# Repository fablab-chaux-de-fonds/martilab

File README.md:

Martilab, fruit d'une collaboration entre le [FabLab Chaux-de-Fonds](fablab-chaux-de-fonds.ch) et le [Muzoo](https://muzoo.ch/) , propose une approche pratique pour encourager la nidification des martinets. En plaçant des haut-parleurs discrets diffusant des signaux sonores adaptés près des nichoirs, nous offrons aux martinets un environnement accueillant et stimulant. Une initiative simple et efficace pour favoriser la préservation de ces oiseaux migrateurs essentiels à notre écosystème. 

<div align="center">

</div>

# Liste des pièces

| | |
| ----------- | ----------- |
|| [Microcontrôleur - Raspberry Pi Pico H](https://www.mouser.ch/ProductDetail/Raspberry-Pi/SC0917?qs=T%252BzbugeAwjjvYEYcRJk%252Bxw%3D%3D): Un microcontrôleur est un dispositif électronique intégré sur une puce (puce microélectronique) qui combine plusieurs composants essentiels pour le traitement de l'information. Il est conçu pour exécuter des tâches spécifiques dans des systèmes électroniques. <br><br>  Le microcontrôleur est le cerveau du martilab. |
||[Horloge temps réel - D1Z RTC - DS1307](https://www.reichelt.com/ch/fr/shield-d1-horloge-temps-r-el-ds1307-d1z-rtc-p266069.html?&trstct=pos_0&nbc=1): Cette horloge temps réel utilise le circuit intégré DS1307 pour fournir une référence temporelle précise à un microcontrôleur. <br><br>  L'horloge permet de connaître le temps absolu et d'activer la l'haut parleur à un moment de la journée.|
||[Piles boutons - CR1220](https://www.reichelt.com/ch/fr/pile-bouton-lithium-c1220-blister-de-5-xcell-cr1220-5x-p365560.html?&trstct=pos_0&nbc=1):  Les piles boutons CR1220 sont des petites piles rondes au lithium. Elles sont souvent utilisées comme source d'alimentation pour des dispositifs électroniques compacts tels que des horloges, des capteurs et d'autres équipements électroniques.  <br><br>  La pile permet à l'horloge de fonctionner même si le contrôleur est en veille. Ainsi, on connait toujours le temps absolu.
||[Lecteur mp3 - DFPlayer Mini](https://www.reichelt.com/ch/fr/arduino-dfplayer-mini-mp3-wav-microsd-karte-ard-dfpayer-mini-p289897.html?&trstct=pos_0&nbc=1): Un lecteur MP3 compact conçu pour être intégré dans des projets électroniques. Il prend en charge la lecture de fichiers audio stockés sur une carte micro SD, offrant une solution simple pour la lecture audio.|
||[Micro haut-parleur - LSM-40A/SQ](https://www.reichelt.com/ch/fr/haut-parleur-en-m-tal-raccord-soud--lsm-40a-sq-p145885.html?&trstct=pos_0&nbc=1): Un micro haut-parleur est un petit haut-parleur conçu pour émettre des sons dans des dispositifs compacts tels que des dispositifs portables, des jouets électroniques, ou d'autres projets électroniques nécessitant une sortie audio.|
||[JST PH 2-Pin Cable Male Header 200mm](https://www.mouser.ch/ProductDetail/Adafruit/3814?qs=%252BEew9%252B0nqrBFmoDCETN4BA%3D%3D): Un câble avec un connecteur mâle JST PH à deux broches de 200 mm de long. Les connecteurs JST PH sont couramment utilisés pour les connexions de puissance ou de données dans les projets électroniques.<br><br> Ce cable permet de relier le lecteur MP3 et le haut-parleur.|
||[Barrette droite à une rangée de broches 2 pôles - JST PH ](https://www.reichelt.com/ch/fr/barrette-droite-une-rang-e-de-broches-2-p-les-grille2-mm-p-les-jst-ph2p-st-p185049.html?&trstct=pos_0&nbc=1): Une barrette de connecteurs droits à une rangée de deux broches, utilisée pour des connexions simples et compactes dans des projets électroniques. Les connecteurs JST PH offrent une connexion sécurisée.<br><br> Connecteur pour le câble, afin de pouvoir facilement débrancher le haut-parleur.
||[Carte micro SDHC](https://www.reichelt.com/ch/fr/carte-micro-sdhc-4-go-intenso-intenso-msdhc4g-p83730.html?&trstct=pos_0&nbc=1): Une carte mémoire au format micro SDHC, utilisée pour stocker des données telles que des fichiers audio, des images ou des données de configuration pour des dispositifs électroniques.|
||[MOSFET PNP -ZVP2106ASTZ](https://eu.mouser.com/ProductDetail/Diodes-Incorporated/ZVP2106ASTZ?qs=wnTfsH77Xs53LehfD70aKA%3D%3D): Un transistor à effet de champ métal-oxyde-semiconducteur (MOSFET) de type PNP, utilisé pour la commutation de puissance dans des circuits électroniques.<br><br>Ce composent permet d'éteindre ([Commutateur à transistor côté haut](https://www.baldengineer.com/low-side-vs-high-side-transistor-switch.html)) le lecteur MP3 lorsque le martilab ne doit pas émettre de son. Ceci permet d'économiser de la batterie.|
||[Boîtier électronique - CB EAC-02-GY](https://www.reichelt.com/ch/fr/bo-tier-lectronique-110-x-70-x-45-mm-gris-cb-eac-02-gy-p317682.html?&trstct=pos_0&nbc=1): Un boîtier électronique conçu pour loger et protéger les composants électroniques d'un projet. Il offre une structure robuste et un espace organisé pour faciliter le montage. 
||[36-pin Male Header Breakaway 10 pieces](https://eu.mouser.com/ProductDetail/Adafruit/392?qs=GURawfaeGuBPkJS%252B96amuQ%3D%3D): Une barrette de connecteurs mâles de 36 broches, pouvant être séparée en sections plus petites. Les headers sont souvent utilisés pour faciliter la connexion entre les cartes électroniques.<br><br> Les pins évitent de devoir souder les dispositifs (Pico, RTC, DFPlayer) afin de pouvoir facilement les recycler et les utiliser dans d'autres projets.|
||[2 x 20 pin Female Headers](https://www.mouser.ch/ProductDetail/Adafruit/5583?qs=T%252BzbugeAwjicPo%2FCTvtw2w%3D%3D): Deux barrettes de connecteurs femelles de 20 broches chacune. Elles sont utilisées pour créer des connexions entre des cartes ou des composants électroniques.

## Option
| | |
| ----------- | ----------- |
| |[LiPo SHIM](https://www.pi-shop.ch/lipo-shim-for-pico): Le LiPo SHIM (Switch Input Module) for Pico est un module conçu spécifiquement pour le Raspberry Pi Pico. Il est destiné à fournir une interface de gestion d'alimentation pour les batteries LiPo (polymère de lithium). Ce module est généralement compact et s'installe facilement sur la carte Raspberry Pi Pico. Il intègre des composants permettant la charge de la batterie LiPo tout en assurant la sécurité de celle-ci, notamment en évitant la surcharge. De plus, le LiPo SHIM peut inclure un interrupteur d'alimentation pour activer ou désactiver l'alimentation du Raspberry Pi Pico, offrant ainsi un contrôle pratique de l'alimentation. Ce type de module est particulièrement utile pour des projets portables nécessitant une alimentation autonome avec des batteries LiPo.
|| [UPS Module](https://www.pi-shop.ch/ups-module-for-raspberry-pi-pico): Un module UPS (alimentation sans interruption) pour Raspberry Pi Pico est un accessoire qui assure une alimentation continue en cas de coupure de courant. Il intègre une batterie rechargeable pour maintenir l'alimentation pendant une durée déterminée, évitant ainsi la perte de données et garantissant un fonctionnement ininterrompu du Raspberry Pi Pico.

# Prototype
Les breadboards ou [platine d'expérimentation](https://fr.wikipedia.org/wiki/Platine_d%27exp%C3%A9rimentation) sont un outil essentiel pour le prototypage électronique en raison de leur facilité d'utilisation, de leur réutilisabilité, de leur facilité de dépannage, de leur flexibilité, de leur rapidité de prototypage et de leur accessibilité. Ils fournissent une plateforme pratique pour tester et développer des circuits électroniques avant de passer à des solutions plus permanentes, comme les [circuits imprimés](https://fr.wikipedia.org/wiki/Circuit_imprim%C3%A9).

# Schéma électrique
Un [schéma électrique](https://fr.wikipedia.org/wiki/Sch%C3%A9ma_%C3%A9lectrique) est une représentation graphique des composants d'un [circuit électrique](https://fr.wikipedia.org/wiki/Circuit_%C3%A9lectrique) et de leurs connexions. Il utilise des symboles normalisés pour représenter des éléments tels que les résistances, les condensateurs, les transistors, les sources d'énergie et les connexions. Ce schéma permet de visualiser la structure et le fonctionnement d'un circuit de manière claire et concise. Les lignes reliant les symboles représentent les connexions électriques entre les composants, décrivant ainsi le cheminement du courant électrique à travers le circuit. Les schémas électriques sont essentiels pour la conception, la documentation et la compréhension des circuits électriques, facilitant la communication entre les ingénieurs, les concepteurs et les techniciens.

# Design du circuit imprimé
Le design du [circuit imprimé (PCB)](https://fr.wikipedia.org/wiki/Circuit_imprim%C3%A9) est le processus de création et de planification d'un agencement spécifique des composants électroniques sur une plaque de circuit imprimé. Il englobe la disposition stratégique des composants tels que les résistances, les condensateurs, les transistors et les connecteurs, ainsi que les pistes conductrices qui les relient de manière à assurer la fonctionnalité électrique du circuit. Le concepteur de PCB prend en compte divers aspects tels que la minimisation des interférences électromagnétiques, la gestion thermique, la facilité de fabrication et d'assemblage, tout en veillant à optimiser l'espace et à répondre aux exigences spécifiques du circuit électronique à concevoir. Un design de circuit imprimé bien réalisé contribue à la performance, à la fiabilité et à la rentabilité globale du produit électronique final.

# Assemblage
Le placement des composants dans le processus de montage d'un PCB implique de positionner précisément les composants électroniques sur la carte en suivant le schéma électrique, soit manuellement, soit à l'aide d'une machine de placement automatique. Ensuite, le soudage des composants se fait pour fixer ceux-ci sur le PCB, que ce soit à travers un processus manuel avec un fer à souder ou à l'aide d'une machine de soudage automatique pour assurer une connexion stable et fiable.

| | |
| ----------- | ----------- |
|| PCB sorti d'usine avec: <br><br> <li> **Substrat** : La base du PCB, généralement en matériau isolant comme le FR4, sur laquelle les autres éléments sont montés. <li> **Pistes conductrices** : Des chemins conducteurs en cuivre qui permettent le passage du courant électrique entre les différents composants. <li> **Pads** : Zones de surface métallique destinées à recevoir et à connecter les pattes des composants électroniques. <li> **Vias** : Connexions métalliques percées à travers le substrat pour relier les pistes de différentes couches du PCB. <li> **Couches internes** : Couches internes de cuivre dans le PCB utilisées pour relier les composants et les pistes sur différentes couches. <li> **Marquages** : Informations imprimées sur le PCB pour identifier les composants, les pistes et d'autres éléments lors du montage et du dépannage.
|| Brasage du MOSFET, de la Résistance R1, du connecteur JST, et le boutton SW1.
|| Brasage des barrettes de connecteurs femelles afin que les modules restent démontables
|image| Brasage du module RCT
|| Connection des barette de connecteurs
|| Fixer le PCB dans le boîtier

# Software

## Circuit Python
[CircuitPython](https://circuitpython.org/) est un environnement de développement open source conçu pour faciliter la programmation des microcontrôleurs et des cartes de développement électronique, notamment celles de la famille Adafruit. Il s'agit d'une version spéciale du langage de programmation Python adaptée pour les systèmes embarqués. CircuitPython offre une interface simple et conviviale, permettant aux utilisateurs de démarrer rapidement avec la programmation sans avoir à se soucier des détails complexes de la configuration matérielle. Il prend en charge une large gamme de périphériques et de capteurs, offrant ainsi une flexibilité pour créer divers projets électroniques, des objets connectés aux dispositifs interactifs. Avec sa simplicité d'utilisation et sa documentation complète, CircuitPython est largement utilisé dans les projets maker, l'éducation et le prototypage rapide d'applications électroniques.

## Installation
### Installer CircuitPython sur le raspberry pi pico. 
Connectez le Raspberry Pi Pico à votre ordinateur via le cable USB.

Pour installer CircuitPython, veuillez suivre les instruction du [Getting started de CircuitPython](https://learn.adafruit.com/welcome-to-circuitpython/installing-circuitpython). 

Dans le cadre de ce projet, nous utilisons la [version 8.2.9](https://adafruit-circuit-python.s3.amazonaws.com/bin/raspberry_pi_pico/en_US/adafruit-circuitpython-raspberry_pi_pico-en_US-8.2.9.uf2).

### Copier code.py et boot.py
* **code.py** :
    Ce fichier est l'endroit où vous placez votre code principal, celui qui sera exécuté dès que le microcontrôleur ou la carte est alimenté ou redémarré.
    Il contient généralement le script principal de votre projet, qui peut contrôler les périphériques, lire des capteurs, effectuer des calculs, etc.
    Le contenu de code.py est exécuté en boucle, ce qui signifie que le code qu'il contient est constamment réexécuté, assurant le fonctionnement continu de votre projet.

* **boot.py** :
    Le fichier boot.py est exécuté une seule fois, juste après que le microcontrôleur ou la carte de développement a été alimenté ou redémarré.
    Il est principalement utilisé pour effectuer des tâches de configuration initiale, telles que l'initialisation des périphériques, la configuration des broches GPIO, ou d'autres paramètres de démarrage.
    Les tâches effectuées dans boot.py sont essentielles pour préparer l'environnement d'exécution avant que le code principal dans code.py ne commence à s'exécuter.

Il faut copier les fichier `code.py` (./software/code.py) et `boot.py` (./software/boot.py) sur le Raspberry Pi Pico.

Plus d'info sur le site de [circuitPython](https://learn.adafruit.com/welcome-to-circuitpython/creating-and-editing-code)

### Installer les dépendances
Coper le dossier `software/lib` sur le Raspberry Pi Pico.

Liste des dépendance: 
*  [Adafruit_CircuitPython_Register](https://github.com/adafruit/Adafruit_CircuitPython_Register): Utilisé pour réduire la consomation electrique, avec la bibliothèque `alarm`
* [Adafruit DS1307 Library](https://docs.circuitpython.org/projects/ds1307/en/latest/index.html): Pour contrôler le module RTC
* [DFPlayer](https://github.com/bablokb/circuitpython-dfplayer): Pour contrôler le module DFPlayer

### Réglage de l'horloge
Afin de régler l'horloge, il faut modifier le fichier `code.py` avec l'heure actuelle. Afin de pouvoir modifier le fichier `code.py`, il faut débrancher le Raspberry Pi Pico, presser le bouton debug, et re-brancher le Raspberry Pi Pico à l'ordinateur. 

Modifiez la ligne `init_time = time.struct_time(yyyy, mm, dd, HH, MM, SS, 0, -1, -1)`, en indiquant la date et l'heure, où 
* *yyyy* est l'année. Par exemple: 2024
* *mm* est le mois en 1 et 12. Par exemple: 2
* *jj* est le jour du mois entre 1 et 31. Par exemple: 25
* *HH* est l'heure entre 1 et 23. Par exemple: 19
* *MM* est la minute entre 1 et 59. Par exemple 59

Une fois la variable `init_time` modifié, vous pouvez sauvegarder le fichier `code.py`. 

Afin d'éviter que l'horloge s'initialise à nouveau, il faut commenter la ligne et re-sauvegarder le fichier `code.py`.

# Publications
[Linkedin](https://www.linkedin.com/feed/update/urn:li:activity:7173920802231193601): MUZOO & Fablab Chaux-de-Fonds au Tecday De La Broye pour faire chanter les martinets. Un partenariat unique alliant découverte des MINT pour les jeunes et préservation de la biodiversité... C'est ce que le MUZOO a réalisé et nous sommes fiers d'avoir été leurs partenaires ! ...

| | | |
| --- | --- | --- |
  |   |  

:camera: Gymnase Intercantonal de la Broye et Mélanie Thomas

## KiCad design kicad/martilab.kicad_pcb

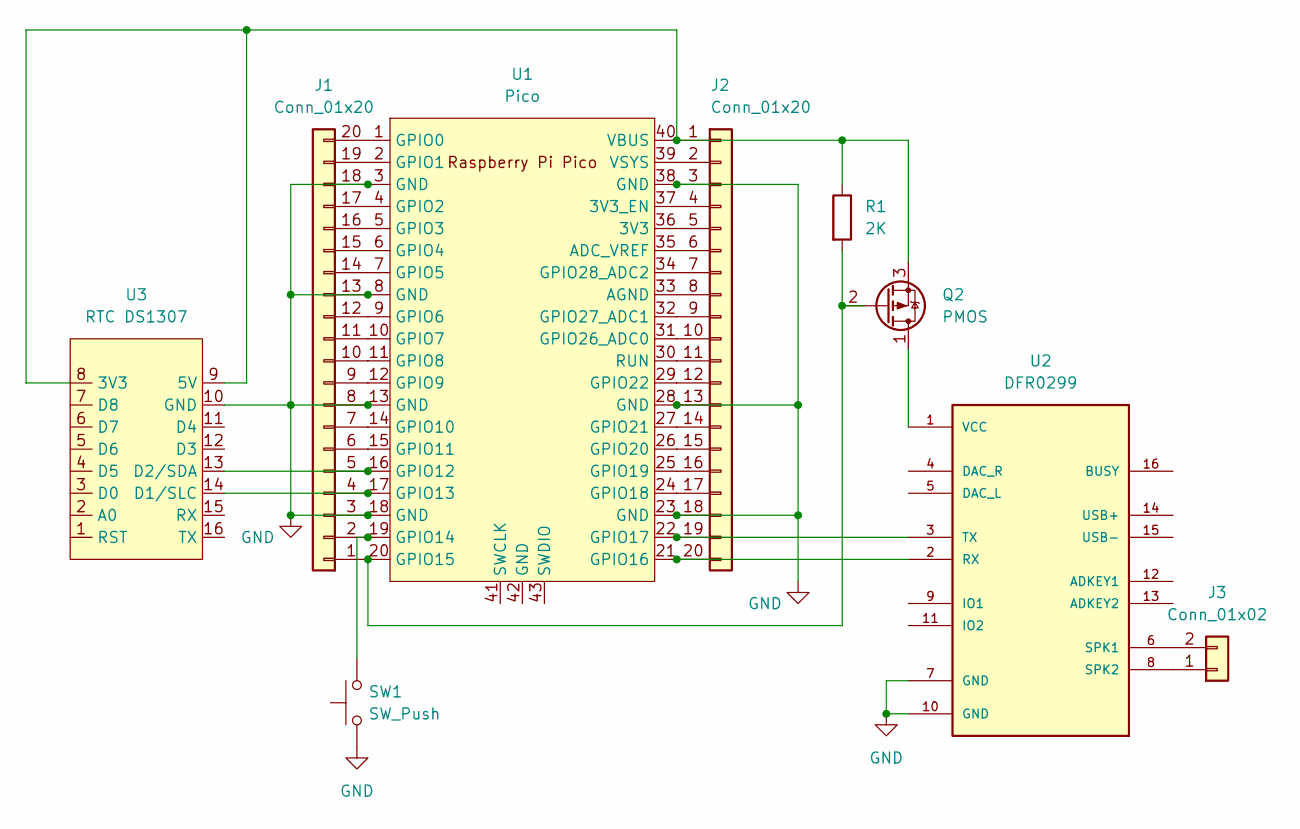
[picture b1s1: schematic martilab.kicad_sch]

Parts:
J1, J2: Conn_01x20; PinHeader_1x20_P2.54mm_Vertical
J3: Conn_01x02; PinSocket_1x02_P2.54mm_Vertical
Q2: PMOS; TO-92_Inline
R1: 2K; R_Axial_DIN0207_L6.3mm_D2.5mm_P7.62mm_Horizontal
SW1: SW_Push; SW_PUSH_6mm
U1: Pico; RPi_Pico_SMD_TH
U2: DFR0299; MODULE_DFR0299
U3: RTC DS1307

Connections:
GND: J1.3, J1.8, J1.13, J1.18, J2.3, J2.13, J2.18, SW1.1, U1.3 (GND), U1.8 (GND), U1.13 (GND), U1.18 (GND), U1.23 (GND), U1.28 (GND), U1.38 (GND), U2.7 (GND), U2.10 (GND), U3.10 (GND)
unnamed: J1.1, Q2.2 (G), R1.2, U1.20 (GPIO15)
unnamed: J1.2, SW1.2, U1.19 (GPIO14)
unnamed: J1.4, U1.17 (GPIO13), U3.14 (D1/SLC)
unnamed: J1.5, U1.16 (GPIO12), U3.13 (D2/SDA)
unnamed: J1.6, U1.15 (GPIO11)
unnamed: J1.7, U1.14 (GPIO10)
unnamed: J1.9, U1.12 (GPIO9)
unnamed: J1.10, U1.11 (GPIO8)
unnamed: J1.11, U1.10 (GPIO7)
unnamed: J1.12, U1.9 (GPIO6)
unnamed: J1.14, U1.7 (GPIO5)
unnamed: J1.15, U1.6 (GPIO4)
unnamed: J1.16, U1.5 (GPIO3)
unnamed: J1.17, U1.4 (GPIO2)
unnamed: J1.19, U1.2 (GPIO1)
unnamed: J1.20, U1.1 (GPIO0)
unnamed: J2.1, Q2.3 (S), R1.1, U1.40 (VBUS), U3.8 (3V3), U3.9 (5V)
unnamed: J2.2, U1.39 (VSYS)
unnamed: J2.4, U1.37 (3V3_EN)
unnamed: J2.5, U1.36 (3V3)
unnamed: J2.6, U1.35 (ADC_VREF)
unnamed: J2.7, U1.34 (GPIO28_ADC2)
unnamed: J2.8, U1.33 (AGND)
unnamed: J2.9, U1.32 (GPIO27_ADC1)
unnamed: J2.10, U1.31 (GPIO26_ADC0)
unnamed: J2.11, U1.30 (RUN)
unnamed: J2.12, U1.29 (GPIO22)
unnamed: J2.14, U1.27 (GPIO21)
unnamed: J2.15, U1.26 (GPIO20)
unnamed: J2.16, U1.25 (GPIO19)
unnamed: J2.17, U1.24 (GPIO18)
unnamed: J2.19, U1.22 (GPIO17), U2.3 (TX)
unnamed: J2.20, U1.21 (GPIO16), U2.2 (RX)
unnamed: J3.1, U2.8 (SPK2)
unnamed: J3.2, U2.6 (SPK1)
unnamed: Q2.1 (D), U2.1 (VCC)

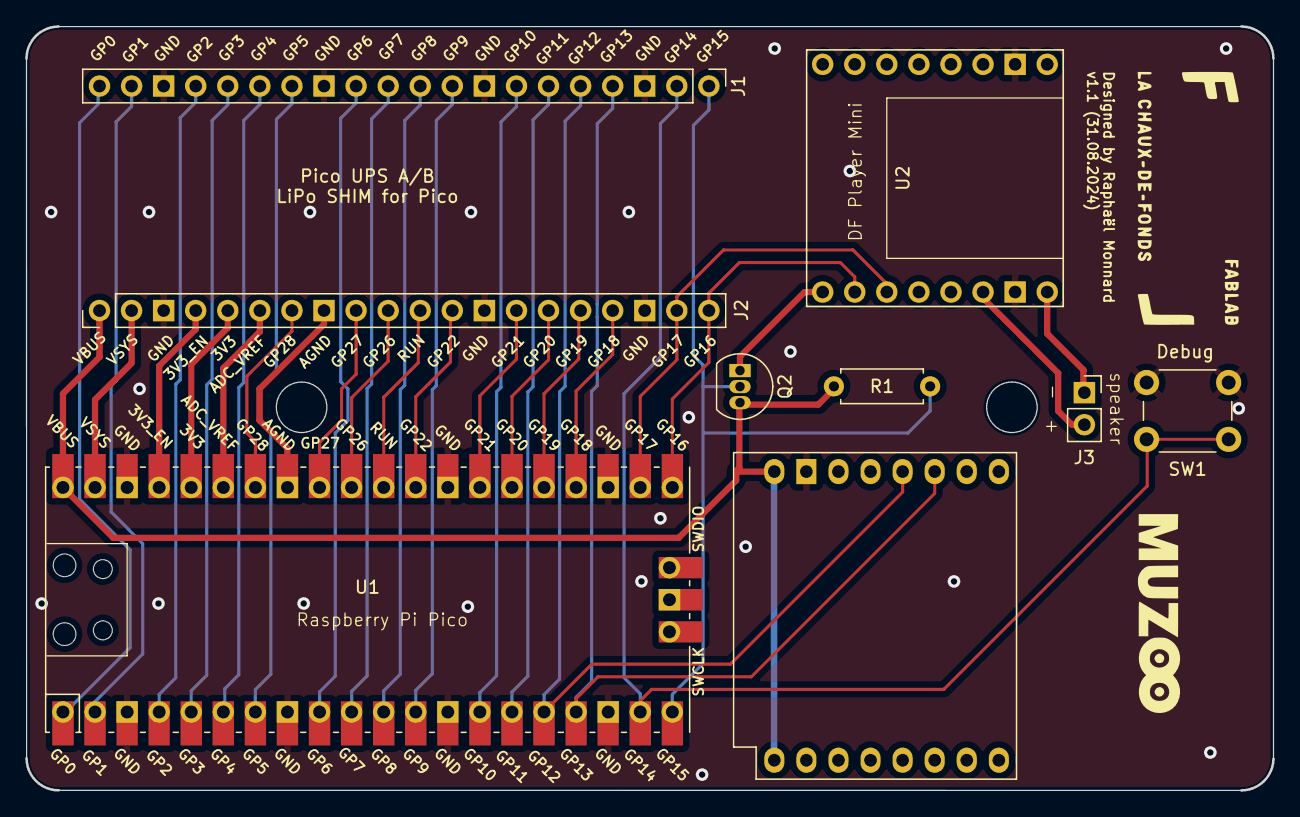
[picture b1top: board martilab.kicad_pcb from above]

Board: 2 copper layers, 98.8 x 60.5 mm, 9 parts (0 on the bottom side), 37 nets.

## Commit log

2024-02-18 init code.py
2024-02-18 add comments
2024-02-18 version 1.0
2024-02-20 Init docs
2024-02-20 fix center images
2024-02-21 add images
2024-02-21 change color to white
2024-02-21 rename logo.svg
2024-02-21 ajout de commentaires
2024-02-21 add schema
2024-02-21 add schema text
2024-02-21 add footprint + battery modules
2024-02-21 add link
2024-03-20 complete documentation
2024-03-20 add log and boot.py
2024-03-20 adjust sleep time
2024-03-20 add dependencies
2024-03-23 ajoute de photos
2024-04-24 test with deep sleep
2024-04-24 remove deep sleep
2024-05-26 Release 2024-05-26
2024-08-31 create v1.1 and add enclosure files
    reduce file size
    add git lfs
2024-10-02 fix restart sound
